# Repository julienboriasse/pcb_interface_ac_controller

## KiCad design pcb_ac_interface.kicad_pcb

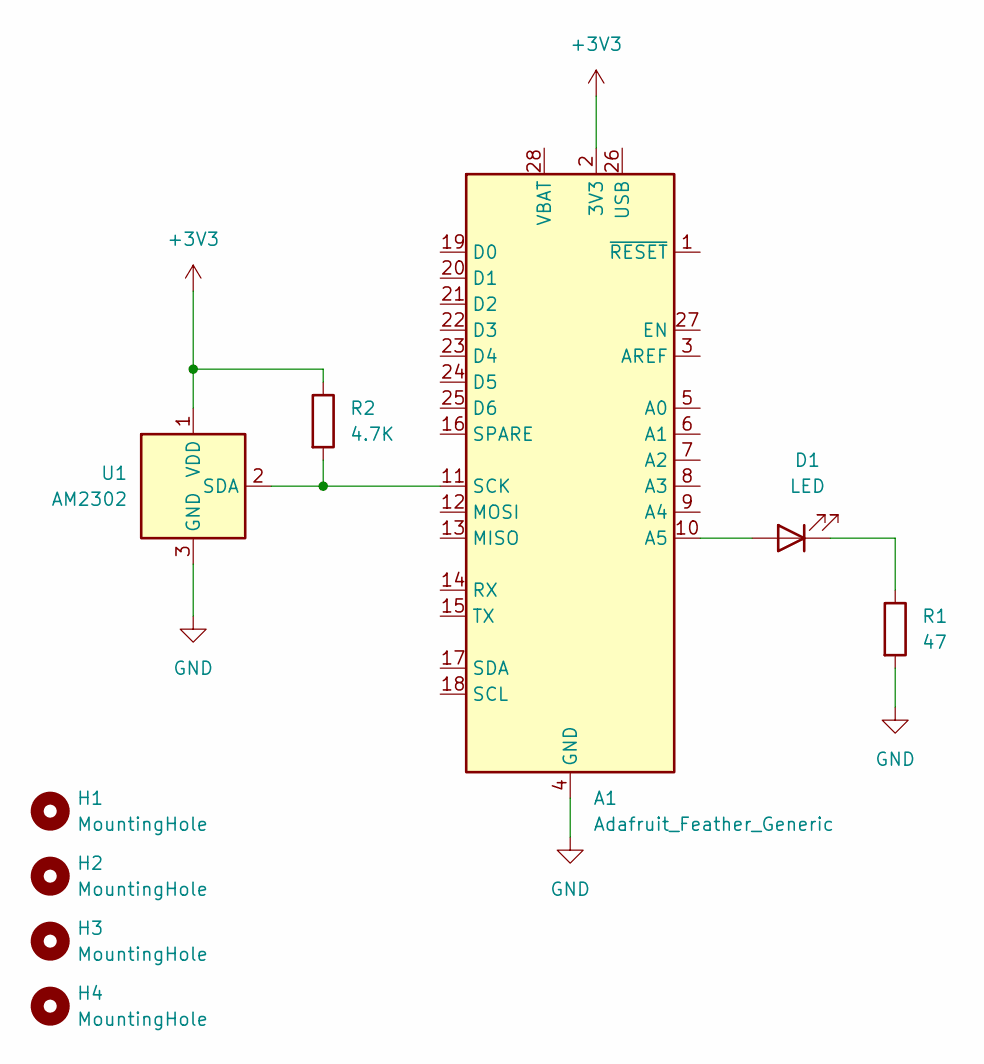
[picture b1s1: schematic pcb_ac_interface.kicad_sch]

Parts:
A1: Adafruit_Feather_Generic; Adafruit_Feather
D1: LED; LED_D5.0mm_Clear
H1, H2, H3, H4: MountingHole; MountingHole_2.1mm
R1: 47; R_Axial_DIN0207_L6.3mm_D2.5mm_P7.62mm_Horizontal
R2: 4.7K; R_Axial_DIN0207_L6.3mm_D2.5mm_P7.62mm_Horizontal
U1: AM2302; ASAIR_AM2302_P2.54mm_Vertical

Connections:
+3V3: A1.2 (3V3), R2.1, U1.1 (VDD)
GND: A1.4 (GND), R1.2, U1.3 (GND), U1.4 (GND)
unnamed: A1.10 (A5), D1.2 (A)
unnamed: A1.11 (SCK), R2.2, U1.2 (SDA)
unnamed: D1.1 (K), R1.1

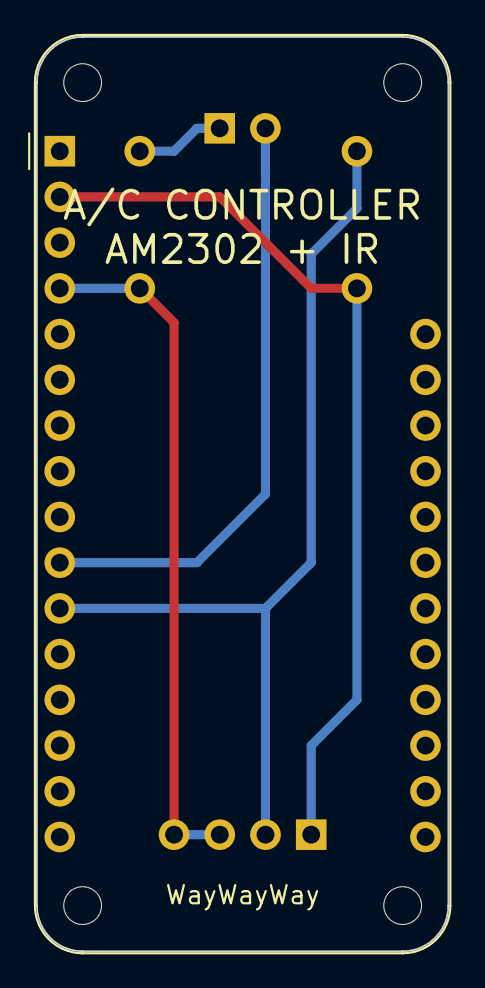
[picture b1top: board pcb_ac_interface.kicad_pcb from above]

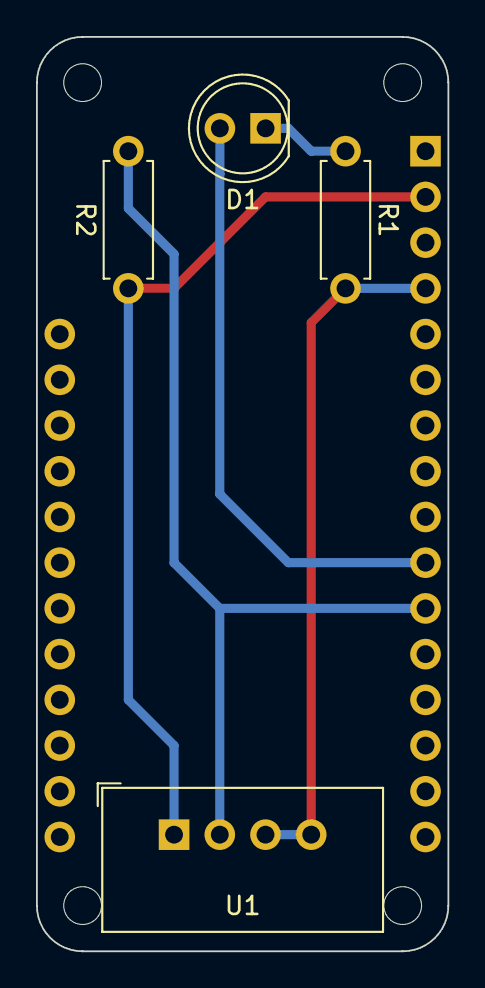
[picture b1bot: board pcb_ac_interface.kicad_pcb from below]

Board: 2 copper layers, 22.9 x 50.8 mm, 9 parts (4 on the bottom side), 5 nets.

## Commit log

2024-01-05 Add all KiCad files
